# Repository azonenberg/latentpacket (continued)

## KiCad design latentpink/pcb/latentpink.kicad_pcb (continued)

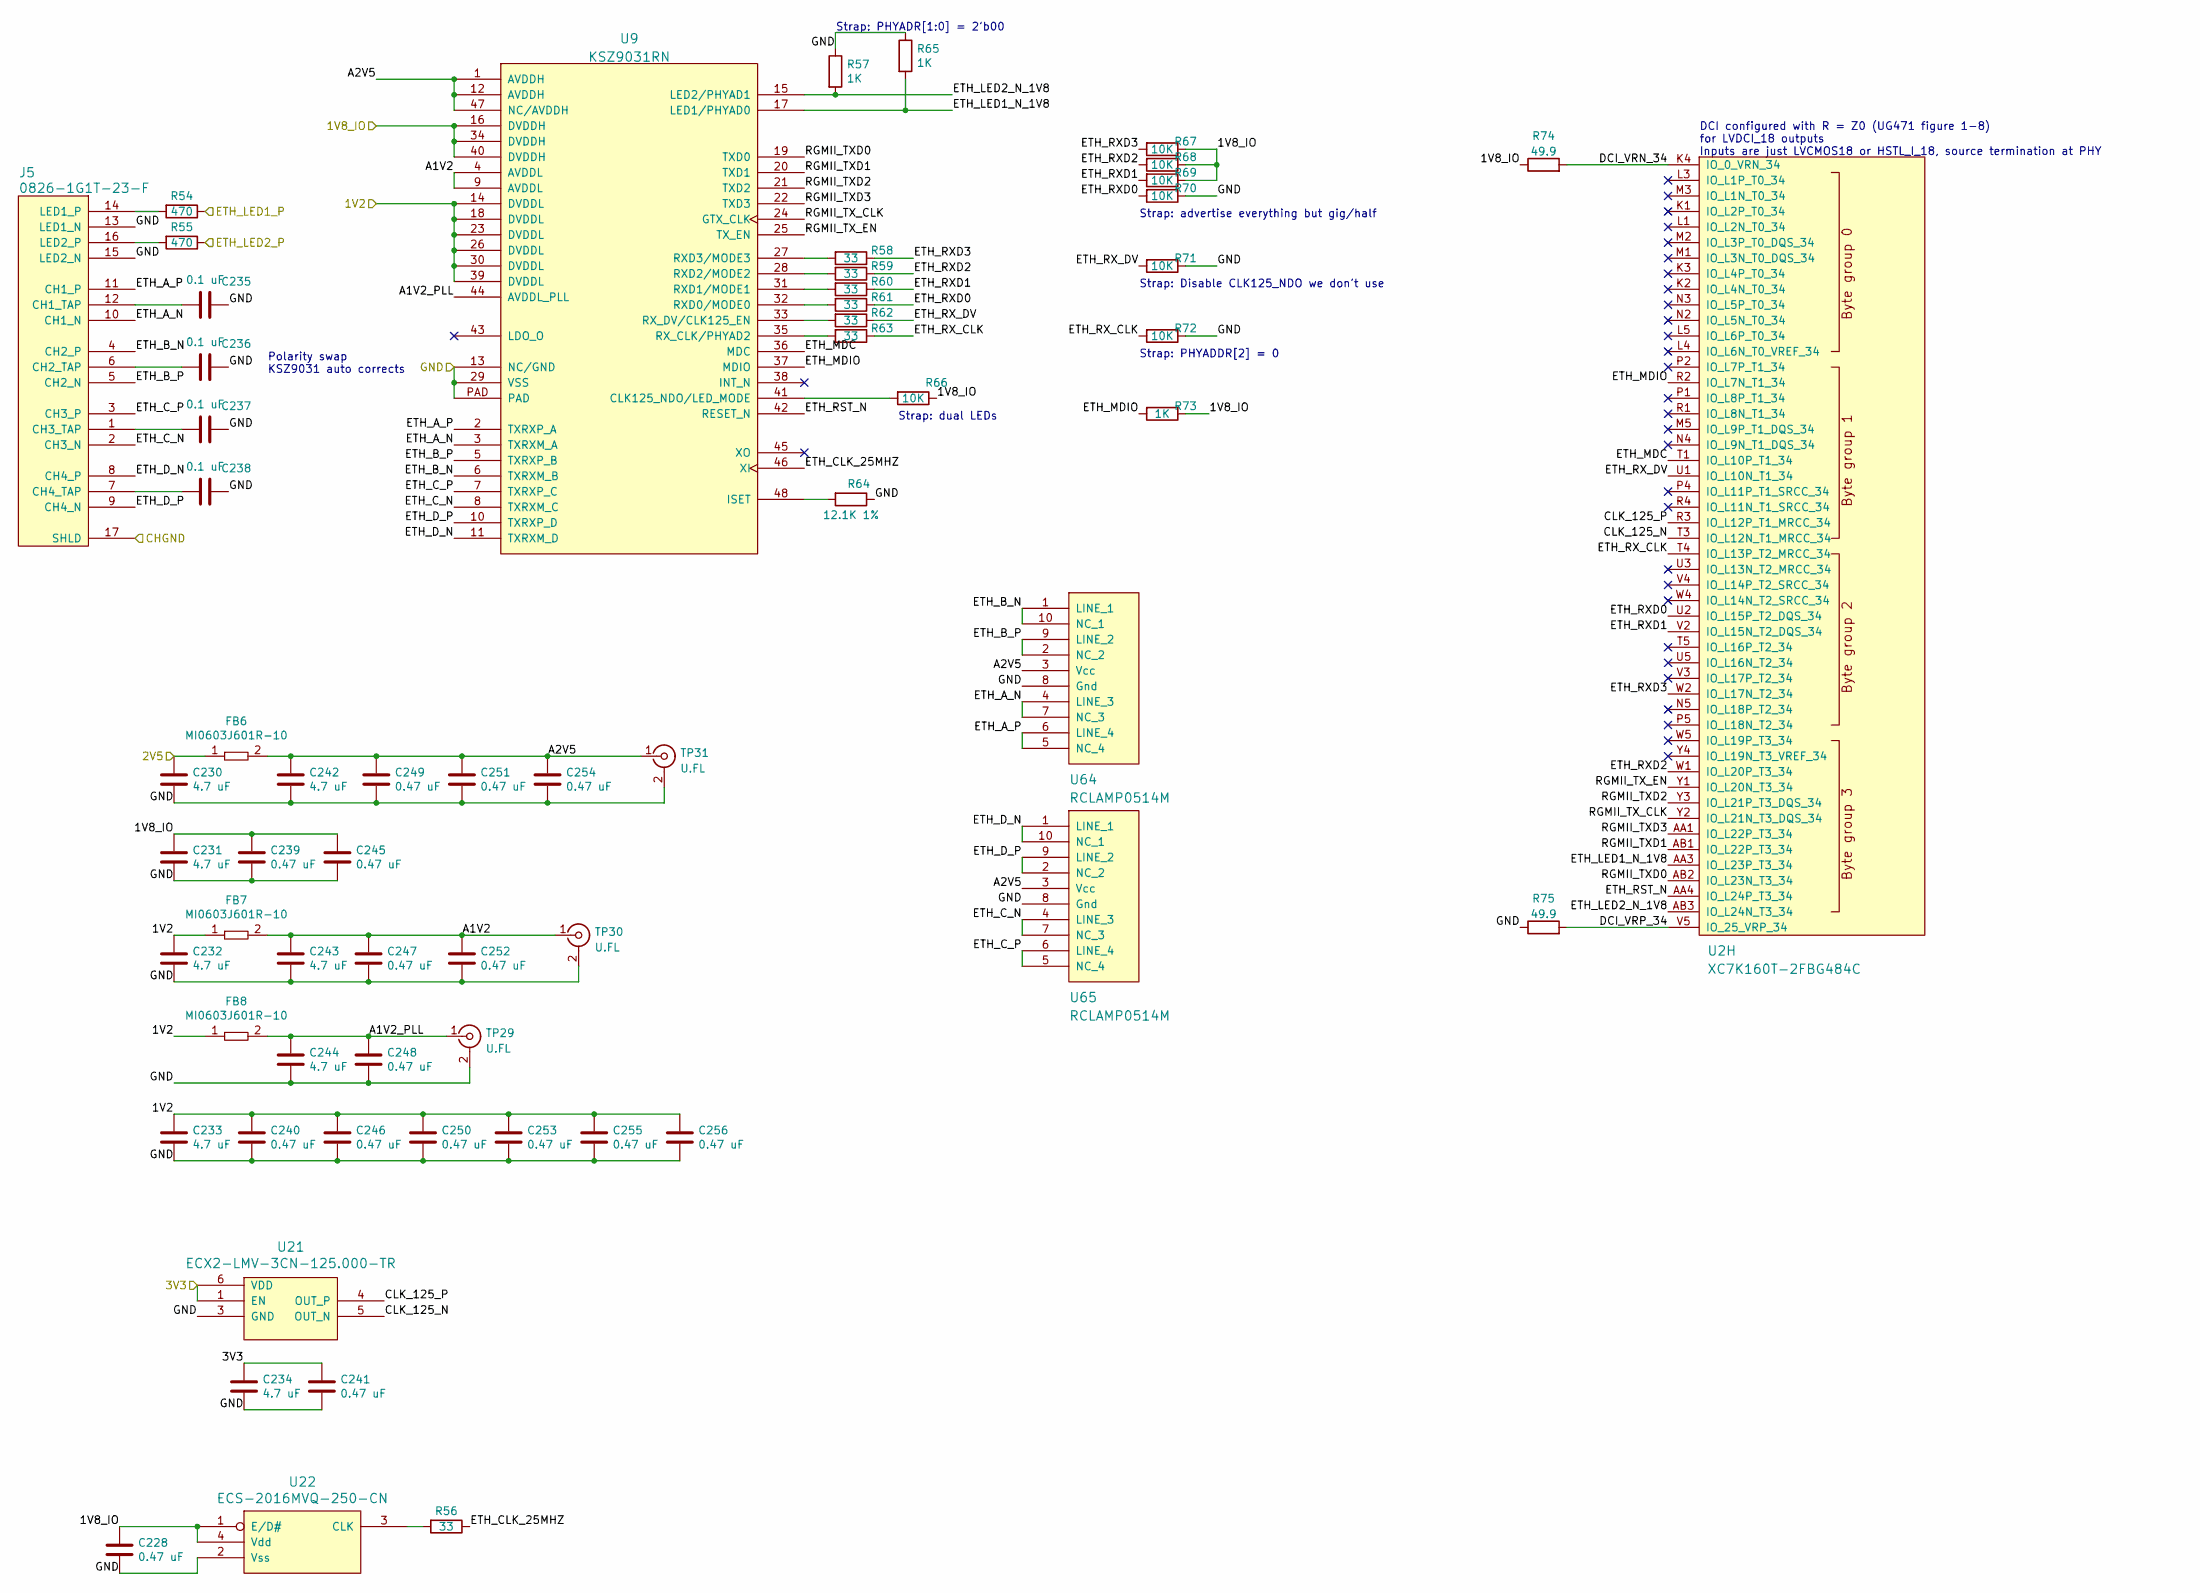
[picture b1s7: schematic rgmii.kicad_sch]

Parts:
C228, C239, C240, C241, C245, C246, C247, C248, C249, C250, C251, C252, C253, C254, C255, C256: 0.47 uF; EIA_0402_CAP_NOSILK
C230, C231, C232, C233, C234, C242, C243, C244: 4.7 uF; EIA_0603_CAP_NOSILK
C235, C236, C237, C238: 0.1 uF; EIA_0402_CAP_NOSILK
FB6, FB7, FB8: MI0603J601R-10; EIA_0603_INDUCTOR_NOSILK
J5: 0826-1G1T-23-F; CONN_BELFUSE_0826_1G1T_23_F
R54, R55: 470; EIA_0402_RES_NOSILK
R56, R58, R59, R60, R61, R62, R63: 33; EIA_0402_RES_NOSILK
R57, R65, R73: 1K; EIA_0402_RES_NOSILK
R64: 12.1K 1%; EIA_0402_RES_NOSILK
R66, R67, R68, R69, R70, R71, R72: 10K; EIA_0402_RES_NOSILK
R74, R75: 49.9; EIA_0402_RES_NOSILK
TP29, TP30, TP31: U.FL; CONN_U.FL_TE_1909763-1
U2: XC7K160T-2FBG484C; BGA_484_22x22_FULLARRAY_1MM
U9: KSZ9031RN; QFN_48_0.5MM_7x7MM
U21: ECX2-LMV-3CN-125.000-TR; OSCILLATOR_LVDS_3.2x2.5
U22: ECS-2016MVQ-250-CN; OSCILLATOR_2.0x1.6
U64, U65: RCLAMP0514M; SOP_10_0.5MM_3MM

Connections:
/1V2: C232.1, C233.1, C240.1, C246.1, C250.1, C253.1, C255.1, C256.1, FB7.1, FB8.1, U9.14 (DVDDL), U9.18 (DVDDL), U9.23 (DVDDL), U9.26 (DVDDL), U9.30 (DVDDL), U9.39 (DVDDL); also elsewhere on the board
/1V8_IO: C228.1, C231.1, C239.1, C245.1, R66.1, R67.1, R68.1, R69.1, R73.1, R74.1, U9.16 (DVDDH), U9.34 (DVDDH), U9.40 (DVDDH), U22.1 (E/D#), U22.4 (Vdd); also elsewhere on the board
/2V5: C230.1, FB6.1; also elsewhere on the board
/3V3: C234.1, C241.1, U21.1 (EN), U21.6 (VDD); also elsewhere on the board
/CHGND: J5.17 (SHLD); also elsewhere on the board
/GND: C228.2, C230.2, C231.2, C232.2, C233.2, C234.2, C235.1, C236.1, C237.1, C238.1, C239.2, C240.2, C241.2, C242.2, C243.2, C244.2, C245.2, C246.2, C247.2, C248.2, C249.2, C250.2, C251.2, C252.2, C253.2, C254.2, C255.2, C256.2, J5.13 (LED1_N), J5.15 (LED2_N), R57.1, R64.1, R65.1, R70.1, R71.1, R72.1, R75.1, TP29.2 (Ext), TP30.2 (Ext), TP31.2 (Ext), U9.13 (NC/GND), U9.29 (VSS), U9.PAD, U21.3 (GND), U22.2 (Vss), U64.8 (Gnd), U65.8 (Gnd); also elsewhere on the board
/Management/ETH_LED1_P: R54.1; also elsewhere on the board
/Management/ETH_LED2_P: R55.1; also elsewhere on the board
/Management/RGMII PHY/A1V2: C243.1, C247.1, C252.1, FB7.2, TP30.1 (In), U9.4 (AVDDL), U9.9 (AVDDL)
/Management/RGMII PHY/A1V2_PLL: C244.1, C248.1, FB8.2, TP29.1 (In), U9.44 (AVDDL_PLL)
/Management/RGMII PHY/A2V5: C242.1, C249.1, C251.1, C254.1, FB6.2, TP31.1 (In), U9.1 (AVDDH), U9.12 (AVDDH), U9.47 (NC/AVDDH), U64.3 (Vcc), U65.3 (Vcc)
/Management/RGMII PHY/CLK_125_N: U2.T3 (IO_L12N_T1_MRCC_34), U21.5 (OUT_N)
/Management/RGMII PHY/CLK_125_P: U2.R3 (IO_L12P_T1_MRCC_34), U21.4 (OUT_P)
/Management/RGMII PHY/DCI_VRN_34: R74.2, U2.K4 (IO_0_VRN_34)
/Management/RGMII PHY/DCI_VRP_34: R75.2, U2.V5 (IO_25_VRP_34)
/Management/RGMII PHY/ETH_A_N: J5.10 (CH1_N), U9.3 (TXRXM_A), U64.4 (LINE_3), U64.7 (NC_3)
/Management/RGMII PHY/ETH_A_P: J5.11 (CH1_P), U9.2 (TXRXP_A), U64.5 (NC_4), U64.6 (LINE_4)
/Management/RGMII PHY/ETH_B_N: J5.4 (CH2_P), U9.6 (TXRXM_B), U64.1 (LINE_1), U64.10 (NC_1)
/Management/RGMII PHY/ETH_B_P: J5.5 (CH2_N), U9.5 (TXRXP_B), U64.2 (NC_2), U64.9 (LINE_2)
/Management/RGMII PHY/ETH_CLK_25MHZ: R56.1, U9.46 (XI)
/Management/RGMII PHY/ETH_C_N: J5.2 (CH3_N), U9.8 (TXRXM_C), U65.4 (LINE_3), U65.7 (NC_3)
/Management/RGMII PHY/ETH_C_P: J5.3 (CH3_P), U9.7 (TXRXP_C), U65.5 (NC_4), U65.6 (LINE_4)
/Management/RGMII PHY/ETH_D_N: J5.8 (CH4_P), U9.11 (TXRXM_D), U65.1 (LINE_1), U65.10 (NC_1)
/Management/RGMII PHY/ETH_D_P: J5.9 (CH4_N), U9.10 (TXRXP_D), U65.2 (NC_2), U65.9 (LINE_2)
/Management/RGMII PHY/ETH_LED1_N_1V8: R65.2, U2.AA3 (IO_L23P_T3_34), U9.17 (LED1/PHYAD0)
/Management/RGMII PHY/ETH_LED2_N_1V8: R57.2, U2.AB3 (IO_L24N_T3_34), U9.15 (LED2/PHYAD1)
/Management/RGMII PHY/ETH_MDC: U2.T1 (IO_L10P_T1_34), U9.36 (MDC)
/Management/RGMII PHY/ETH_MDIO: R73.2, U2.R2 (IO_L7N_T1_34), U9.37 (MDIO)
/Management/RGMII PHY/ETH_RST_N: U2.AA4 (IO_L24P_T3_34), U9.42 (RESET_N)
/Management/RGMII PHY/ETH_RXD0: R61.1, R70.2, U2.U2 (IO_L15P_T2_DQS_34)
/Management/RGMII PHY/ETH_RXD1: R60.1, R69.2, U2.V2 (IO_L15N_T2_DQS_34)
/Management/RGMII PHY/ETH_RXD2: R59.1, R68.2, U2.W1 (IO_L20P_T3_34)
/Management/RGMII PHY/ETH_RXD3: R58.1, R67.2, U2.W2 (IO_L17N_T2_34)
/Management/RGMII PHY/ETH_RX_CLK: R63.1, R72.2, U2.T4 (IO_L13P_T2_MRCC_34)
/Management/RGMII PHY/ETH_RX_DV: R62.1, R71.2, U2.U1 (IO_L10N_T1_34)
/Management/RGMII PHY/RGMII_TXD0: U2.AB2 (IO_L23N_T3_34), U9.19 (TXD0)
/Management/RGMII PHY/RGMII_TXD1: U2.AB1 (IO_L22P_T3_34), U9.20 (TXD1)
/Management/RGMII PHY/RGMII_TXD2: U2.Y3 (IO_L21P_T3_DQS_34), U9.21 (TXD2)
/Management/RGMII PHY/RGMII_TXD3: U2.AA1 (IO_L22P_T3_34), U9.22 (TXD3)
/Management/RGMII PHY/RGMII_TX_CLK: U2.Y2 (IO_L21N_T3_DQS_34), U9.24 (GTX_CLK)
/Management/RGMII PHY/RGMII_TX_EN: U2.Y1 (IO_L20N_T3_34), U9.25 (TX_EN)
unnamed: C235.2, J5.12 (CH1_TAP)
unnamed: C236.2, J5.6 (CH2_TAP)
unnamed: C237.2, J5.1 (CH3_TAP)
unnamed: C238.2, J5.7 (CH4_TAP)
unnamed: J5.14 (LED1_P), R54.2
unnamed: J5.16 (LED2_P), R55.2
unnamed: R56.2, U22.3 (CLK)
unnamed: R58.2, U9.27 (RXD3/MODE3)
unnamed: R59.2, U9.28 (RXD2/MODE2)
unnamed: R60.2, U9.31 (RXD1/MODE1)
unnamed: R61.2, U9.32 (RXD0/MODE0)
unnamed: R62.2, U9.33 (RX_DV/CLK125_EN)
unnamed: R63.2, U9.35 (RX_CLK/PHYAD2)
unnamed: R66.2, U9.41 (CLK125_NDO/LED_MODE)
unnamed: R64.2, U9.48 (ISET)

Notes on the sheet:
Strap: Disable CLK125_NDO we don't use
Polarity swap KSZ9031 auto corrects
Strap: PHYADR[1:0] = 2'b00
Strap: advertise everything but gig/half
Strap: PHYADDR[2] = 0
Strap: dual LEDs
DCI configured with R = Z0 (UG471 figure 1-8) for LVDCI_18 outputs Inputs are just LVCMOS18 or HSTL_I_18, source termination at PHY

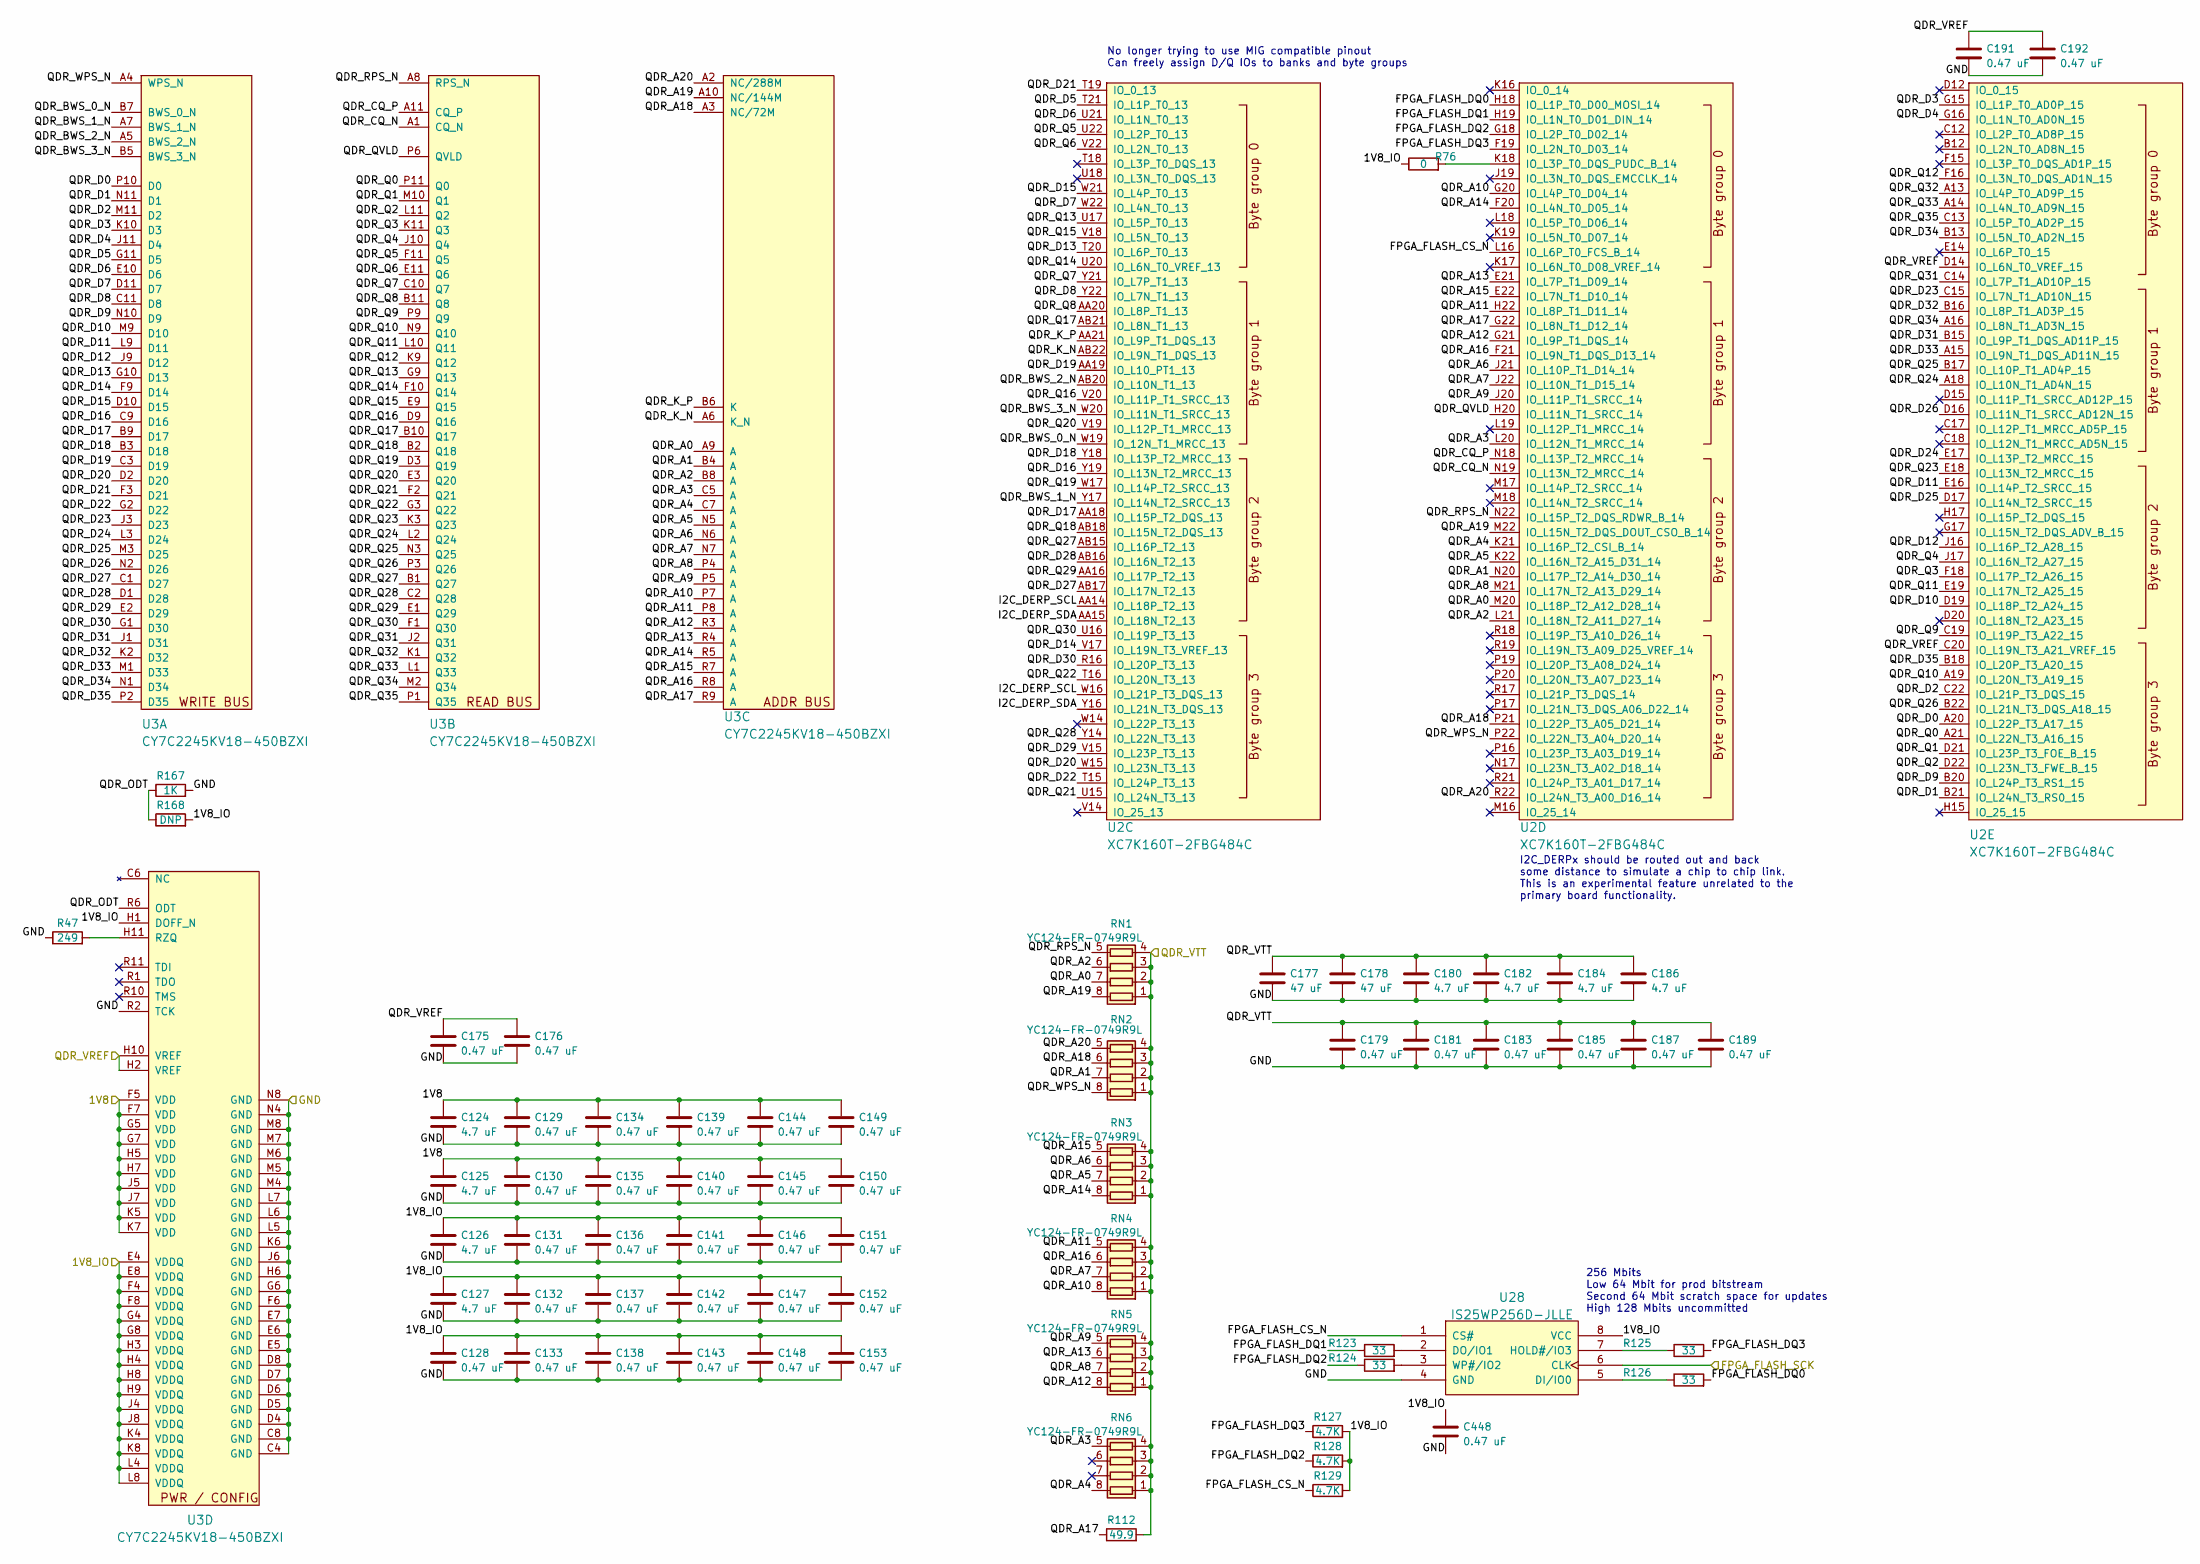
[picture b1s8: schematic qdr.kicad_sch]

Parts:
C124, C125, C126, C127, C180, C182, C184, C186: 4.7 uF; EIA_0603_CAP_NOSILK
C128, C129, C130, C131, C132, C133, C134, C135, C136, C137, C138, C139, C140, C141, C142, C143, C144, C145, C146, C147, C148, C149, C150, C151, C152, C153, C175, C176, C179, C181, C183, C185, C187, C189, C191, C192, C448: 0.47 uF; EIA_0402_CAP_NOSILK
C177, C178: 47 uF; EIA_1206_CAP_NOSILK
R47: 249; EIA_0402_RES_NOSILK
R76: 0; EIA_0402_RES_NOSILK
R112: 49.9; EIA_0402_RES_NOSILK
R123, R124, R125, R126: 33; EIA_0402_RES_NOSILK
R127, R128, R129: 4.7K; EIA_0402_RES_NOSILK
R167: 1K; EIA_0402_RES_NOSILK
R168: DNP; EIA_0402_RES_NOSILK
RN1, RN2, RN3, RN4, RN5, RN6: YC124-FR-0749R9L; YAGEO_YC124-FR
U2: XC7K160T-2FBG484C; BGA_484_22x22_FULLARRAY_1MM
U3: CY7C2245KV18-450BZXI; BGA_165_11x15_FULLARRAY_1MM
U28: IS25WP256D-JLLE; DFN_8_1.27MM_8x6MM

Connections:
/1V8: C124.1, C125.1, C129.1, C130.1, C134.1, C135.1, C139.1, C140.1, C144.1, C145.1, C149.1, C150.1, U3.F5 (VDD), U3.F7 (VDD), U3.G5 (VDD), U3.G7 (VDD), U3.H5 (VDD), U3.H7 (VDD), U3.J5 (VDD), U3.J7 (VDD), U3.K5 (VDD), U3.K7 (VDD); also elsewhere on the board
/1V8_IO: C126.1, C127.1, C128.1, C131.1, C132.1, C133.1, C136.1, C137.1, C138.1, C141.1, C142.1, C143.1, C146.1, C147.1, C148.1, C151.1, C152.1, C153.1, C448.1, R76.1, R127.2, R128.2, R129.2, R168.2, U3.E4 (VDDQ), U3.E8 (VDDQ), U3.F4 (VDDQ), U3.F8 (VDDQ), U3.G4 (VDDQ), U3.G8 (VDDQ), U3.H1 (DOFF_N), U3.H3 (VDDQ), U3.H4 (VDDQ), U3.H8 (VDDQ), U3.H9 (VDDQ), U3.J4 (VDDQ), U3.J8 (VDDQ), U3.K4 (VDDQ), U3.K8 (VDDQ), U3.L4 (VDDQ), U3.L8 (VDDQ), U28.8 (VCC); also elsewhere on the board
/FPGA/FPGA_FLASH_SCK: U28.6 (CLK); also elsewhere on the board
/FPGA/QDR SRAM/FPGA_FLASH_CS_N: R129.1, U2.L16 (IO_L6P_T0_FCS_B_14), U28.1 (CS#)
/FPGA/QDR SRAM/FPGA_FLASH_DQ0: R126.2, U2.H18 (IO_L1P_T0_D00_MOSI_14)
/FPGA/QDR SRAM/FPGA_FLASH_DQ1: R123.1, U2.H19 (IO_L1N_T0_D01_DIN_14)
/FPGA/QDR SRAM/FPGA_FLASH_DQ2: R124.1, R128.1, U2.G18 (IO_L2P_T0_D02_14)
/FPGA/QDR SRAM/FPGA_FLASH_DQ3: R125.2, R127.1, U2.F19 (IO_L2N_T0_D03_14)
/FPGA/QDR SRAM/I2C_DERP_SCL: U2.AA14 (IO_L18P_T2_13), U2.W16 (IO_L21P_T3_DQS_13)
/FPGA/QDR SRAM/I2C_DERP_SDA: U2.AA15 (IO_L18N_T2_13), U2.Y16 (IO_L21N_T3_DQS_13)
/FPGA/QDR SRAM/QDR_A0: RN1.7 (R2.2), U2.M20 (IO_L18P_T2_A12_D28_14), U3.A9 (A)
/FPGA/QDR SRAM/QDR_A1: RN2.7 (R2.2), U2.N20 (IO_L17P_T2_A14_D30_14), U3.B4 (A)
/FPGA/QDR SRAM/QDR_A2: RN1.6 (R3.2), U2.L21 (IO_L18N_T2_A11_D27_14), U3.B8 (A)
/FPGA/QDR SRAM/QDR_A3: RN6.5 (R4.2), U2.L20 (IO_L12N_T1_MRCC_14), U3.C5 (A)
/FPGA/QDR SRAM/QDR_A4: RN6.8 (R1.2), U2.K21 (IO_L16P_T2_CSI_B_14), U3.C7 (A)
/FPGA/QDR SRAM/QDR_A5: RN3.7 (R2.2), U2.K22 (IO_L16N_T2_A15_D31_14), U3.N5 (A)
/FPGA/QDR SRAM/QDR_A6: RN3.6 (R3.2), U2.J21 (IO_L10P_T1_D14_14), U3.N6 (A)
/FPGA/QDR SRAM/QDR_A7: RN4.7 (R2.2), U2.J22 (IO_L10N_T1_D15_14), U3.N7 (A)
/FPGA/QDR SRAM/QDR_A8: RN5.7 (R2.2), U2.M21 (IO_L17N_T2_A13_D29_14), U3.P4 (A)
/FPGA/QDR SRAM/QDR_A9: RN5.5 (R4.2), U2.J20 (IO_L11P_T1_SRCC_14), U3.P5 (A)
/FPGA/QDR SRAM/QDR_A10: RN4.8 (R1.2), U2.G20 (IO_L4P_T0_D04_14), U3.P7 (A)
/FPGA/QDR SRAM/QDR_A11: RN4.5 (R4.2), U2.H22 (IO_L8P_T1_D11_14), U3.P8 (A)
/FPGA/QDR SRAM/QDR_A12: RN5.8 (R1.2), U2.G21 (IO_L9P_T1_DQS_14), U3.R3 (A)
/FPGA/QDR SRAM/QDR_A13: RN5.6 (R3.2), U2.E21 (IO_L7P_T1_D09_14), U3.R4 (A)
/FPGA/QDR SRAM/QDR_A14: RN3.8 (R1.2), U2.F20 (IO_L4N_T0_D05_14), U3.R5 (A)
/FPGA/QDR SRAM/QDR_A15: RN3.5 (R4.2), U2.E22 (IO_L7N_T1_D10_14), U3.R7 (A)
/FPGA/QDR SRAM/QDR_A16: RN4.6 (R3.2), U2.F21 (IO_L9N_T1_DQS_D13_14), U3.R8 (A)
/FPGA/QDR SRAM/QDR_A17: R112.1, U2.G22 (IO_L8N_T1_D12_14), U3.R9 (A)
/FPGA/QDR SRAM/QDR_A18: RN2.6 (R3.2), U2.P21 (IO_L22P_T3_A05_D21_14), U3.A3 (NC/72M)
/FPGA/QDR SRAM/QDR_A19: RN1.8 (R1.2), U2.M22 (IO_L15N_T2_DQS_DOUT_CSO_B_14), U3.A10 (NC/144M)
/FPGA/QDR SRAM/QDR_A20: RN2.5 (R4.2), U2.R22 (IO_L24N_T3_A00_D16_14), U3.A2 (NC/288M)
/FPGA/QDR SRAM/QDR_BWS_0_N: U2.W19 (IO_12N_T1_MRCC_13), U3.B7 (BWS_0_N)
/FPGA/QDR SRAM/QDR_BWS_1_N: U2.Y17 (IO_L14N_T2_SRCC_13), U3.A7 (BWS_1_N)
/FPGA/QDR SRAM/QDR_BWS_2_N: U2.AB20 (IO_L10N_T1_13), U3.A5 (BWS_2_N)
/FPGA/QDR SRAM/QDR_BWS_3_N: U2.W20 (IO_L11N_T1_SRCC_13), U3.B5 (BWS_3_N)
/FPGA/QDR SRAM/QDR_CQ_N: U2.N19 (IO_L13N_T2_MRCC_14), U3.A1 (CQ_N)
/FPGA/QDR SRAM/QDR_CQ_P: U2.N18 (IO_L13P_T2_MRCC_14), U3.A11 (CQ_P)
/FPGA/QDR SRAM/QDR_D0: U2.A20 (IO_L22P_T3_A17_15), U3.P10 (D0)
/FPGA/QDR SRAM/QDR_D1: U2.B21 (IO_L24N_T3_RS0_15), U3.N11 (D1)
/FPGA/QDR SRAM/QDR_D2: U2.C22 (IO_L21P_T3_DQS_15), U3.M11 (D2)
/FPGA/QDR SRAM/QDR_D3: U2.G15 (IO_L1P_T0_AD0P_15), U3.K10 (D3)
/FPGA/QDR SRAM/QDR_D4: U2.G16 (IO_L1N_T0_AD0N_15), U3.J11 (D4)
/FPGA/QDR SRAM/QDR_D5: U2.T21 (IO_L1P_T0_13), U3.G11 (D5)
/FPGA/QDR SRAM/QDR_D6: U2.U21 (IO_L1N_T0_13), U3.E10 (D6)
/FPGA/QDR SRAM/QDR_D7: U2.W22 (IO_L4N_T0_13), U3.D11 (D7)
/FPGA/QDR SRAM/QDR_D8: U2.Y22 (IO_L7N_T1_13), U3.C11 (D8)
/FPGA/QDR SRAM/QDR_D9: U2.B20 (IO_L24P_T3_RS1_15), U3.N10 (D9)
/FPGA/QDR SRAM/QDR_D10: U2.D19 (IO_L18P_T2_A24_15), U3.M9 (D10)
/FPGA/QDR SRAM/QDR_D11: U2.E16 (IO_L14P_T2_SRCC_15), U3.L9 (D11)
/FPGA/QDR SRAM/QDR_D12: U2.J16 (IO_L16P_T2_A28_15), U3.J9 (D12)
/FPGA/QDR SRAM/QDR_D13: U2.T20 (IO_L6P_T0_13), U3.G10 (D13)
/FPGA/QDR SRAM/QDR_D14: U2.V17 (IO_L19N_T3_VREF_13), U3.F9 (D14)
/FPGA/QDR SRAM/QDR_D15: U2.W21 (IO_L4P_T0_13), U3.D10 (D15)
/FPGA/QDR SRAM/QDR_D16: U2.Y19 (IO_L13N_T2_MRCC_13), U3.C9 (D16)
/FPGA/QDR SRAM/QDR_D17: U2.AA18 (IO_L15P_T2_DQS_13), U3.B9 (D17)
/FPGA/QDR SRAM/QDR_D18: U2.Y18 (IO_L13P_T2_MRCC_13), U3.B3 (D18)
/FPGA/QDR SRAM/QDR_D19: U2.AA19 (IO_L10_PT1_13), U3.C3 (D19)
/FPGA/QDR SRAM/QDR_D20: U2.W15 (IO_L23N_T3_13), U3.D2 (D20)
/FPGA/QDR SRAM/QDR_D21: U2.T19 (IO_0_13), U3.F3 (D21)
/FPGA/QDR SRAM/QDR_D22: U2.T15 (IO_L24P_T3_13), U3.G2 (D22)
/FPGA/QDR SRAM/QDR_D23: U2.C15 (IO_L7N_T1_AD10N_15), U3.J3 (D23)
/FPGA/QDR SRAM/QDR_D24: U2.E17 (IO_L13P_T2_MRCC_15), U3.L3 (D24)
/FPGA/QDR SRAM/QDR_D25: U2.D17 (IO_L14N_T2_SRCC_15), U3.M3 (D25)
/FPGA/QDR SRAM/QDR_D26: U2.D16 (IO_L11N_T1_SRCC_AD12N_15), U3.N2 (D26)
/FPGA/QDR SRAM/QDR_D27: U2.AB17 (IO_L17N_T2_13), U3.C1 (D27)
/FPGA/QDR SRAM/QDR_D28: U2.AB16 (IO_L16N_T2_13), U3.D1 (D28)
/FPGA/QDR SRAM/QDR_D29: U2.V15 (IO_L23P_T3_13), U3.E2 (D29)
/FPGA/QDR SRAM/QDR_D30: U2.R16 (IO_L20P_T3_13), U3.G1 (D30)
/FPGA/QDR SRAM/QDR_D31: U2.B15 (IO_L9P_T1_DQS_AD11P_15), U3.J1 (D31)
/FPGA/QDR SRAM/QDR_D32: U2.B16 (IO_L8P_T1_AD3P_15), U3.K2 (D32)
/FPGA/QDR SRAM/QDR_D33: U2.A15 (IO_L9N_T1_DQS_AD11N_15), U3.M1 (D33)
/FPGA/QDR SRAM/QDR_D34: U2.B13 (IO_L5N_T0_AD2N_15), U3.N1 (D34)
/FPGA/QDR SRAM/QDR_D35: U2.B18 (IO_L20P_T3_A20_15), U3.P2 (D35)
/FPGA/QDR SRAM/QDR_K_N: U2.AB22 (IO_L9N_T1_DQS_13), U3.A6 (K_N)
/FPGA/QDR SRAM/QDR_K_P: U2.AA21 (IO_L9P_T1_DQS_13), U3.B6 (K)
/FPGA/QDR SRAM/QDR_ODT: R167.1, R168.1, U3.R6 (ODT)
/FPGA/QDR SRAM/QDR_Q0: U2.A21 (IO_L22N_T3_A16_15), U3.P11 (Q0)
/FPGA/QDR SRAM/QDR_Q1: U2.D21 (IO_L23P_T3_FOE_B_15), U3.M10 (Q1)
/FPGA/QDR SRAM/QDR_Q2: U2.D22 (IO_L23N_T3_FWE_B_15), U3.L11 (Q2)
/FPGA/QDR SRAM/QDR_Q3: U2.F18 (IO_L17P_T2_A26_15), U3.K11 (Q3)
/FPGA/QDR SRAM/QDR_Q4: U2.J17 (IO_L16N_T2_A27_15), U3.J10 (Q4)
/FPGA/QDR SRAM/QDR_Q5: U2.U22 (IO_L2P_T0_13), U3.F11 (Q5)
/FPGA/QDR SRAM/QDR_Q6: U2.V22 (IO_L2N_T0_13), U3.E11 (Q6)
/FPGA/QDR SRAM/QDR_Q7: U2.Y21 (IO_L7P_T1_13), U3.C10 (Q7)
/FPGA/QDR SRAM/QDR_Q8: U2.AA20 (IO_L8P_T1_13), U3.B11 (Q8)
/FPGA/QDR SRAM/QDR_Q9: U2.C19 (IO_L19P_T3_A22_15), U3.P9 (Q9)
/FPGA/QDR SRAM/QDR_Q10: U2.A19 (IO_L20N_T3_A19_15), U3.N9 (Q10)
/FPGA/QDR SRAM/QDR_Q11: U2.E19 (IO_L17N_T2_A25_15), U3.L10 (Q11)
/FPGA/QDR SRAM/QDR_Q12: U2.F16 (IO_L3N_T0_DQS_AD1N_15), U3.K9 (Q12)
/FPGA/QDR SRAM/QDR_Q13: U2.U17 (IO_L5P_T0_13), U3.G9 (Q13)
/FPGA/QDR SRAM/QDR_Q14: U2.U20 (IO_L6N_T0_VREF_13), U3.F10 (Q14)
/FPGA/QDR SRAM/QDR_Q15: U2.V18 (IO_L5N_T0_13), U3.E9 (Q15)
/FPGA/QDR SRAM/QDR_Q16: U2.V20 (IO_L11P_T1_SRCC_13), U3.D9 (Q16)
/FPGA/QDR SRAM/QDR_Q17: U2.AB21 (IO_L8N_T1_13), U3.B10 (Q17)
/FPGA/QDR SRAM/QDR_Q18: U2.AB18 (IO_L15N_T2_DQS_13), U3.B2 (Q18)
/FPGA/QDR SRAM/QDR_Q19: U2.W17 (IO_L14P_T2_SRCC_13), U3.D3 (Q19)
/FPGA/QDR SRAM/QDR_Q20: U2.V19 (IO_L12P_T1_MRCC_13), U3.E3 (Q20)
/FPGA/QDR SRAM/QDR_Q21: U2.U15 (IO_L24N_T3_13), U3.F2 (Q21)
/FPGA/QDR SRAM/QDR_Q22: U2.T16 (IO_L20N_T3_13), U3.G3 (Q22)
/FPGA/QDR SRAM/QDR_Q23: U2.E18 (IO_L13N_T2_MRCC_15), U3.K3 (Q23)
/FPGA/QDR SRAM/QDR_Q24: U2.A18 (IO_L10N_T1_AD4N_15), U3.L2 (Q24)
/FPGA/QDR SRAM/QDR_Q25: U2.B17 (IO_L10P_T1_AD4P_15), U3.N3 (Q25)
/FPGA/QDR SRAM/QDR_Q26: U2.B22 (IO_L21N_T3_DQS_A18_15), U3.P3 (Q26)
/FPGA/QDR SRAM/QDR_Q27: U2.AB15 (IO_L16P_T2_13), U3.B1 (Q27)
/FPGA/QDR SRAM/QDR_Q28: U2.Y14 (IO_L22N_T3_13), U3.C2 (Q28)
/FPGA/QDR SRAM/QDR_Q29: U2.AA16 (IO_L17P_T2_13), U3.E1 (Q29)
/FPGA/QDR SRAM/QDR_Q30: U2.U16 (IO_L19P_T3_13), U3.F1 (Q30)
/FPGA/QDR SRAM/QDR_Q31: U2.C14 (IO_L7P_T1_AD10P_15), U3.J2 (Q31)
/FPGA/QDR SRAM/QDR_Q32: U2.A13 (IO_L4P_T0_AD9P_15), U3.K1 (Q32)
/FPGA/QDR SRAM/QDR_Q33: U2.A14 (IO_L4N_T0_AD9N_15), U3.L1 (Q33)
/FPGA/QDR SRAM/QDR_Q34: U2.A16 (IO_L8N_T1_AD3N_15), U3.M2 (Q34)
/FPGA/QDR SRAM/QDR_Q35: U2.C13 (IO_L5P_T0_AD2P_15), U3.P1 (Q35)
/FPGA/QDR SRAM/QDR_QVLD: U2.H20 (IO_L11N_T1_SRCC_14), U3.P6 (QVLD)
/FPGA/QDR SRAM/QDR_RPS_N: RN1.5 (R4.2), U2.N22 (IO_L15P_T2_DQS_RDWR_B_14), U3.A8 (RPS_N)
/FPGA/QDR SRAM/QDR_WPS_N: RN2.8 (R1.2), U2.P22 (IO_L22N_T3_A04_D20_14), U3.A4 (WPS_N)
/GND: C124.2, C125.2, C126.2, C127.2, C128.2, C129.2, C130.2, C131.2, C132.2, C133.2, C134.2, C135.2, C136.2, C137.2, C138.2, C139.2, C140.2, C141.2, C142.2, C143.2, C144.2, C145.2, C146.2, C147.2, C148.2, C149.2, C150.2, C151.2, C152.2, C153.2, C175.2, C176.2, C177.2, C178.2, C179.2, C180.2, C181.2, C182.2, C183.2, C184.2, C185.2, C186.2, C187.2, C189.2, C191.2, C192.2, C448.2, R47.1, R167.2, U3.C4 (GND), U3.C8 (GND), U3.D4 (GND), U3.D5 (GND), U3.D6 (GND), U3.D7 (GND), U3.D8 (GND), U3.E5 (GND), U3.E6 (GND), U3.E7 (GND), U3.F6 (GND), U3.G6 (GND), U3.H6 (GND), U3.J6 (GND), U3.K6 (GND), U3.L5 (GND), U3.L6 (GND), U3.L7 (GND), U3.M4 (GND), U3.M5 (GND), U3.M6 (GND), U3.M7 (GND), U3.M8 (GND), U3.N4 (GND), U3.N8 (GND), U3.R2 (TCK), U28.4 (GND); also elsewhere on the board
/QDR_VREF: C175.1, C176.1, C191.1, C192.1, U2.C20 (IO_L19N_T3_A21_VREF_15), U2.D14 (IO_L6N_T0_VREF_15), U3.H2 (VREF), U3.H10 (VREF); also elsewhere on the board
/QDR_VTT: C177.1, C178.1, C179.1, C180.1, C181.1, C182.1, C183.1, C184.1, C185.1, C186.1, C187.1, C189.1, R112.2, RN1.1 (R1.1), RN1.2 (R2.1), RN1.3 (R3.1), RN1.4 (R4.1), RN2.1 (R1.1), RN2.2 (R2.1), RN2.3 (R3.1), RN2.4 (R4.1), RN3.1 (R1.1), RN3.2 (R2.1), RN3.3 (R3.1), RN3.4 (R4.1), RN4.1 (R1.1), RN4.2 (R2.1), RN4.3 (R3.1), RN4.4 (R4.1), RN5.1 (R1.1), RN5.2 (R2.1), RN5.3 (R3.1), RN5.4 (R4.1), RN6.1 (R1.1), RN6.2 (R2.1), RN6.3 (R3.1), RN6.4 (R4.1); also elsewhere on the board
unnamed: R47.2, U3.H11 (RZQ)
unnamed: R76.2, U2.K18 (IO_L3P_T0_DQS_PUDC_B_14)
unnamed: R123.2, U28.2 (DO/IO1)
unnamed: R124.2, U28.3 (WP#/IO2)
unnamed: R125.1, U28.7 (HOLD#/IO3)
unnamed: R126.1, U28.5 (DI/IO0)

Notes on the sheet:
No longer trying to use MIG compatible pinout Can freely assign D/Q IOs to banks and byte groups
I2C_DERPx should be routed out and back some distance to simulate a chip to chip link. This is an experimental feature unrelated to the primary board functionality.
256 Mbits Low 64 Mbit for prod bitstream Second 64 Mbit scratch space for updates High 128 Mbits uncommitted

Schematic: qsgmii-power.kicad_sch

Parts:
C1: 330 uF; EIA_1210_CAP_NOSILK
C2, C3, C4, C5, C7, C9, C10, C11, C12, C14, C16, C17, C18, C19, C21, C23, C24, C25, C26, C27, C28, C30, C31, C32, C33, C34, C35, C37, C38, C39, C40, C41, C42, C44, C45, C46, C47, C48, C49, C50, C51, C52, C53, C54, C55, C56, C57, C58, C59, C60, C61, C62, C63, C64, C65, C66, C68, C69, C71, C72, C74, C75, C77, C78, C79, C80, C81, C82, C83, C84, C85, C86, C87, C88, C264, C266, C268, C269, C270, C271, C272, C273, C274, C275, C276, C277, C278, C279, C280, C281, C282, C285, C286, C287, C288, C290, C291, C294, C295, C296, C297, C298, C299, C300, C302, C303, C304, C305, C307, C308, C309, C310, C312, C313, C314, C315, C316, C317, C318, C319, C320, C321, C322, C323, C324, C325, C326, C327, C328, C329, C330, C331, C332, C333: 0.47 uF; EIA_0402_CAP_NOSILK
C6: 47 uF; EIA_1206_CAP_NOSILK
C8, C13, C15, C20, C22, C29, C36, C43, C70, C73, C76, C267, C292, C293, C306, C311: 4.7 uF; EIA_0603_CAP_NOSILK
C67, C289, C301: 47 uF; EIA_1210_CAP_NOSILK
C262, C263, C265, C284: 22 uF; EIA_0805_CAP_NOSILK
C283: 22 uF; EIA_1206_CAP_NOSILK
L2, L3, L4, L5: HI1206N101R-10; EIA_1206_CAP_NOSILK
TP36, TP37, TP38, TP39: U.FL; CONN_U.FL_TE_1909763-1
U1: VSC8512; BGA_672_27x27_DEPOPCORNER_1MM

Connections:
/1V0: C1.1, C2.1, C3.1, C4.1, C5.1, C8.1, C9.1, C10.1, C11.1, C12.1, C15.1, C16.1, C17.1, C18.1, C19.1, C22.1, C23.1, C24.1, C25.1, C26.1, C29.1, C30.1, C31.1, C32.1, C33.1, C36.1, C37.1, C38.1, C39.1, C40.1, C43.1, C44.1, C45.1, C46.1, C47.1, C50.1, C51.1, C52.1, C53.1, C56.1, C57.1, C58.1, C59.1, C62.1, C63.1, C64.1, C65.1, C262.1, C263.1, C284.1, L2.2, L3.2, L5.2, U1.G6 (VDD), U1.G7 (VDD), U1.G8 (VDD), U1.G11 (VDD), U1.G12 (VDD), U1.G15 (VDD), U1.G16 (VDD), U1.G19 (VDD), U1.G20 (VDD), U1.G21 (VDD), U1.H6 (VDD), U1.H7 (VDD), U1.H8 (VDD), U1.H9 (VDD), U1.H10 (VDD), U1.H11 (VDD), U1.H12 (VDD), U1.H15 (VDD), U1.H16 (VDD), U1.H17 (VDD), U1.H18 (VDD), U1.H19 (VDD), U1.H20 (VDD), U1.H21 (VDD), U1.L6 (VDD), U1.L7 (VDD), U1.L20 (VDD), U1.L21 (VDD), U1.M6 (VDD), U1.M7 (VDD), U1.M20 (VDD), U1.M21 (VDD), U1.N6 (VDD), U1.N7 (VDD), U1.N20 (VDD), U1.N21 (VDD), U1.P6 (VDD), U1.P7 (VDD), U1.P20 (VDD), U1.P21 (VDD), U1.R6 (VDD), U1.R7 (VDD), U1.R20 (VDD), U1.R21 (VDD), U1.T6 (VDD), U1.T7 (VDD), U1.T20 (VDD), U1.T21 (VDD), U1.V6 (VDD), U1.V7 (VDD), U1.V8 (VDD), U1.V9 (VDD), U1.V10 (VDD), U1.V11 (VDD), U1.V12 (VDD), U1.V13 (VDD), U1.V14 (VDD), U1.V15 (VDD), U1.V16 (VDD), U1.V17 (VDD), U1.V18 (VDD), U1.V19 (VDD), U1.V20 (VDD), U1.V21 (VDD), U1.W6 (VDD), U1.W7 (VDD), U1.W8 (VDD), U1.W9 (VDD), U1.W10 (VDD), U1.W11 (VDD), U1.W12 (VDD), U1.W13 (VDD), U1.W14 (VDD), U1.W15 (VDD), U1.W16 (VDD), U1.W17 (VDD), U1.W18 (VDD), U1.W19 (VDD), U1.W20 (VDD), U1.W21 (VDD); also elsewhere on the board
/2V5: C283.1, C301.1, C302.1, C303.1, C306.1, C307.1, C308.1, C311.1, C312.1, C313.1, C316.1, C317.1, C318.1, C321.1, C322.1, C323.1, C324.1, C325.1, C328.1, C329.1, C330.1, C331.1, C332.1, C333.1, L4.2, U1.AA5 (VDD_IO), U1.AB5 (VDD_IO), U1.AC4 (VDD_IO), U1.AC5 (VDD_IO), U1.AD4 (VDD_IO), U1.AE3 (VDD_IO), U1.AF2 (VDD_IO), U1.E6 (VDD_IO), U1.E7 (VDD_IO), U1.E20 (VDD_IO), U1.E21 (VDD_IO), U1.F6 (VDD_IO), U1.F21 (VDD_IO), U1.P5 (VDD_IO), U1.R5 (VDD_IO), U1.T5 (VDD_IO), U1.U5 (VDD_IO), U1.V5 (VDD_IO), U1.W5 (VDD_IO), U1.Y5 (VDD_IO); also elsewhere on the board
/GND: C1.2, C2.2, C3.2, C4.2, C5.2, C6.2, C7.2, C8.2, C9.2, C10.2, C11.2, C12.2, C13.2, C14.2, C15.2, C16.2, C17.2, C18.2, C19.2, C20.2, C21.2, C22.2, C23.2, C24.2, C25.2, C26.2, C27.2, C28.2, C29.2, C30.2, C31.2, C32.2, C33.2, C34.2, C35.2, C36.2, C37.2, C38.2, C39.2, C40.2, C41.2, C42.2, C43.2, C44.2, C45.2, C46.2, C47.2, C48.2, C49.2, C50.2, C51.2, C52.2, C53.2, C54.2, C55.2, C56.2, C57.2, C58.2, C59.2, C60.2, C61.2, C62.2, C63.2, C64.2, C65.2, C66.2, C67.2, C68.2, C69.2, C70.2, C71.2, C72.2, C73.2, C74.2, C75.2, C76.2, C77.2, C78.2, C79.2, C80.2, C81.2, C82.2, C83.2, C84.2, C85.2, C86.2, C87.2, C88.2, C262.2, C263.2, C264.2, C265.2, C266.2, C267.2, C268.2, C269.2, C270.2, C271.2, C272.2, C273.2, C274.2, C275.2, C276.2, C277.2, C278.2, C279.2, C280.2, C281.2, C282.2, C283.2, C284.2, C285.2, C286.2, C287.2, C288.2, C289.2, C290.2, C291.2, C292.2, C293.2, C294.2, C295.2, C296.2, C297.2, C298.2, C299.2, C300.2, C301.2, C302.2, C303.2, C304.2, C305.2, C306.2, C307.2, C308.2, C309.2, C310.2, C311.2, C312.2, C313.2, C314.2, C315.2, C316.2, C317.2, C318.2, C319.2, C320.2, C321.2, C322.2, C323.2, C324.2, C325.2, C326.2, C327.2, C328.2, C329.2, C330.2, C331.2, C332.2, C333.2, TP36.2 (Ext), TP37.2 (Ext), TP38.2 (Ext), TP39.2 (Ext), U1.AA12 (VSS), U1.AA16 (VSS), U1.AA20 (VSS), U1.AA22 (VDD_IODDR), U1.AB6 (VSS), U1.AB7 (VSS), U1.AB8 (VSS), U1.AB9 (VSS), U1.AB10 (VSS), U1.AB11 (VSS), U1.AB12 (VSS), U1.AB13 (VSS), U1.AB14 (VSS), U1.AB15 (VSS), U1.AB16 (VSS), U1.AB17 (VSS), U1.AB18 (VSS), U1.AB19 (VSS), U1.AB20 (VSS), U1.AB21 (VSS), U1.AB22 (VDD_IODDR), U1.AC3 (VSS), U1.AC22 (VDD_IODDR), U1.AD5 (VSS), U1.AD22 (VSS), U1.AD23 (VDD_IODDR), U1.AE1 (VSS), U1.AE4 (VSS), U1.AE5 (VSS), U1.AE12 (VSS), U1.AE16 (VSS), U1.AE20 (VSS), U1.AE23 (VSS), U1.AE24 (VDD_IODDR), U1.AE26 (VSS), U1.AF5 (VSS), U1.AF12 (VSS), U1.AF16 (VSS), U1.AF20 (VSS), U1.AF23 (VSS), U1.AF24 (VDD_IODDR), U1.AF25 (VDD_IODDR), U1.B1 (VSS), U1.B26 (VSS), U1.C6 (RSVD_VSS), U1.G3 (VSS), U1.G5 (VSS), U1.G22 (VSS), U1.G24 (VSS), U1.H3 (VSS), U1.H5 (VSS), U1.H22 (VSS), U1.H24 (VSS), U1.K3 (VSS), U1.K8 (VSS), U1.K9 (VSS), U1.K10 (VSS), U1.K11 (VSS), U1.K12 (VSS), U1.K13 (VSS), U1.K14 (VSS), U1.K15 (VSS), U1.K16 (VSS), U1.K17 (VSS), U1.K18 (VSS), U1.K19 (VSS), U1.K24 (VSS), U1.L3 (VSS), U1.L5 (VSS), U1.L8 (VSS), U1.L9 (VSS), U1.L10 (VSS), U1.L11 (VSS), U1.L12 (VSS), U1.L13 (VSS), U1.L14 (VSS), U1.L15 (VSS), U1.L16 (VSS), U1.L17 (VSS), U1.L18 (VSS), U1.L19 (VSS), U1.L22 (VSS), U1.L24 (VSS), U1.M8 (VSS), U1.M9 (VSS), U1.M10 (VSS), U1.M11 (VSS), U1.M12 (VSS), U1.M13 (VSS), U1.M14 (VSS), U1.M15 (VSS), U1.M16 (VSS), U1.M17 (VSS), U1.M18 (VSS), U1.M19 (VSS), U1.N3 (VSS), U1.N4 (VSS), U1.N5 (VSS), U1.N8 (VSS), U1.N9 (VSS), U1.N10 (VSS), U1.N11 (VSS), U1.N12 (VSS), U1.N13 (VSS), U1.N14 (VSS), U1.N15 (VSS), U1.N16 (VSS), U1.N17 (VSS), U1.N18 (VSS), U1.N19 (VSS), U1.N22 (VSS), U1.N23 (VSS), U1.N24 (VSS), U1.P3 (VSS), U1.P8 (VSS), U1.P9 (VSS), U1.P10 (VSS), U1.P11 (VSS), U1.P12 (VSS), U1.P13 (VSS), U1.P14 (VSS), U1.P15 (VSS), U1.P16 (VSS), U1.P17 (VSS), U1.P18 (VSS), U1.P19 (VSS), U1.P22 (VDD_IODDR), U1.P23 (VSS), U1.P24 (VSS), U1.R8 (VSS), U1.R9 (VSS), U1.R10 (VSS), U1.R11 (VSS), U1.R12 (VSS), U1.R13 (VSS), U1.R14 (VSS), U1.R15 (VSS), U1.R16 (VSS), U1.R17 (VSS), U1.R18 (VSS), U1.R19 (VSS), U1.R22 (VDD_IODDR), U1.T8 (VSS), U1.T9 (VSS), U1.T10 (VSS), U1.T11 (VSS), U1.T12 (VSS), U1.T13 (VSS), U1.T14 (VSS), U1.T15 (VSS), U1.T16 (VSS), U1.T17 (VSS), U1.T18 (VSS), U1.T19 (VSS), U1.T22 (VDD_IODDR), U1.U6 (VSS), U1.U7 (VSS), U1.U8 (VSS), U1.U9 (VSS), U1.U10 (VSS), U1.U11 (VSS), U1.U12 (VSS), U1.U13 (VSS), U1.U14 (VSS), U1.U15 (VSS), U1.U16 (VSS), U1.U17 (VSS), U1.U18 (VSS), U1.U19 (VSS), U1.U20 (VSS), U1.U21 (VSS), U1.U22 (VDD_IODDR), U1.V22 (VDD_IODDR), U1.W22 (VDD_IODDR), U1.Y12 (VSS), U1.Y16 (VSS), U1.Y20 (VSS), U1.Y22 (VDD_IODDR); also elsewhere on the board
/QSGMII PHY/QSGMII Power/A1V0_VSC: C264.1, C265.1, C266.1, C267.1, C268.1, C269.1, C270.1, C271.1, C272.1, C273.1, C274.1, C275.1, C276.1, C277.1, C278.1, C279.1, C280.1, C281.1, C282.1, C285.1, C286.1, C287.1, C288.1, C290.1, C291.1, C294.1, L3.1, TP37.1 (In), U1.E9 (VDD_AL), U1.E10 (VDD_AL), U1.E17 (VDD_AL), U1.E18 (VDD_AL), U1.F9 (VDD_AL), U1.F10 (VDD_AL), U1.F17 (VDD_AL), U1.F18 (VDD_AL), U1.G9 (VDD_AL), U1.G10 (VDD_AL), U1.G17 (VDD_AL), U1.G18 (VDD_AL), U1.J5 (VDD_AL), U1.J6 (VDD_AL), U1.J7 (VDD_AL), U1.J20 (VDD_AL), U1.J21 (VDD_AL), U1.J22 (VDD_AL), U1.K5 (VDD_AL), U1.K6 (VDD_AL), U1.K7 (VDD_AL), U1.K20 (VDD_AL), U1.K21 (VDD_AL), U1.K22 (VDD_AL)
/QSGMII PHY/QSGMII Power/A1V0_VSC_SERDES1: C6.1, C7.1, C13.1, C14.1, C20.1, C21.1, C27.1, C28.1, C34.1, C35.1, C41.1, C42.1, C48.1, C49.1, C54.1, C55.1, C60.1, C61.1, C66.1, L2.1, TP36.1 (In), U1.AC6 (VDD_A), U1.AC7 (VDD_A), U1.AC8 (VDD_A), U1.AC9 (VDD_A), U1.AC10 (VDD_A), U1.AC11 (VDD_A), U1.AC12 (VDD_A), U1.AC13 (VDD_A), U1.AC14 (VDD_A), U1.AC15 (VDD_A), U1.AC16 (VDD_A), U1.AC17 (VDD_A), U1.AC18 (VDD_A), U1.AC19 (VDD_A), U1.AC20 (VDD_A), U1.AC21 (VDD_A)
/QSGMII PHY/QSGMII Power/A1V0_VSC_SERDES2: C289.1, C292.1, C293.1, C295.1, C296.1, C297.1, C298.1, C299.1, C300.1, C304.1, C305.1, C309.1, C310.1, C314.1, C315.1, C319.1, C320.1, C326.1, C327.1, L5.1, TP39.1 (In), U1.AD6 (VDD_VS), U1.AD7 (VDD_VS), U1.AD8 (VDD_VS), U1.AD9 (VDD_VS), U1.AD10 (VDD_VS), U1.AD11 (VDD_VS), U1.AD12 (VDD_VS), U1.AD13 (VDD_VS), U1.AD14 (VDD_VS), U1.AD15 (VDD_VS), U1.AD16 (VDD_VS), U1.AD17 (VDD_VS), U1.AD18 (VDD_VS), U1.AD19 (VDD_VS), U1.AD20 (VDD_VS), U1.AD21 (VDD_VS)
/QSGMII PHY/QSGMII Power/A2V5_VSC: C67.1, C68.1, C69.1, C70.1, C71.1, C72.1, C73.1, C74.1, C75.1, C76.1, C77.1, C78.1, C79.1, C80.1, C81.1, C82.1, C83.1, C84.1, C85.1, C86.1, C87.1, C88.1, L4.1, TP38.1 (In), U1.D4 (VDD_AH), U1.D5 (VDD_AH), U1.D11 (VDD_AH), U1.D16 (VDD_AH), U1.E4 (VDD_AH), U1.E5 (VDD_AH), U1.E8 (VDD_AH), U1.E11 (VDD_AH), U1.E12 (VDD_AH), U1.E15 (VDD_AH), U1.E16 (VDD_AH), U1.E19 (VDD_AH), U1.E22 (VDD_AH), U1.E23 (VDD_AH), U1.F4 (VDD_AH), U1.F5 (VDD_AH), U1.F7 (VDD_AH), U1.F8 (VDD_AH), U1.F11 (VDD_AH), U1.F12 (VDD_AH), U1.F15 (VDD_AH), U1.F16 (VDD_AH), U1.F19 (VDD_AH), U1.F20 (VDD_AH), U1.F22 (VDD_AH), U1.F23 (VDD_AH), U1.J3 (VDD_AH), U1.J4 (VDD_AH), U1.J23 (VDD_AH), U1.J24 (VDD_AH), U1.M3 (VDD_AH), U1.M4 (VDD_AH), U1.M5 (VDD_AH), U1.M22 (VDD_AH), U1.M23 (VDD_AH), U1.M24 (VDD_AH)

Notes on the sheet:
VDD_AL decoupling
Ferrites 80-100 ohms @ 100 MHz Vendor recommends: Panasonic EXCELSA39 (thru hole) Steward HI1206N101R-00 (EOL)
VDD_A decoupling
VDD_VS decoupling
VDD_AH decoupling
VDD decoupling
TODO: can we shove more caps on A2V5?
